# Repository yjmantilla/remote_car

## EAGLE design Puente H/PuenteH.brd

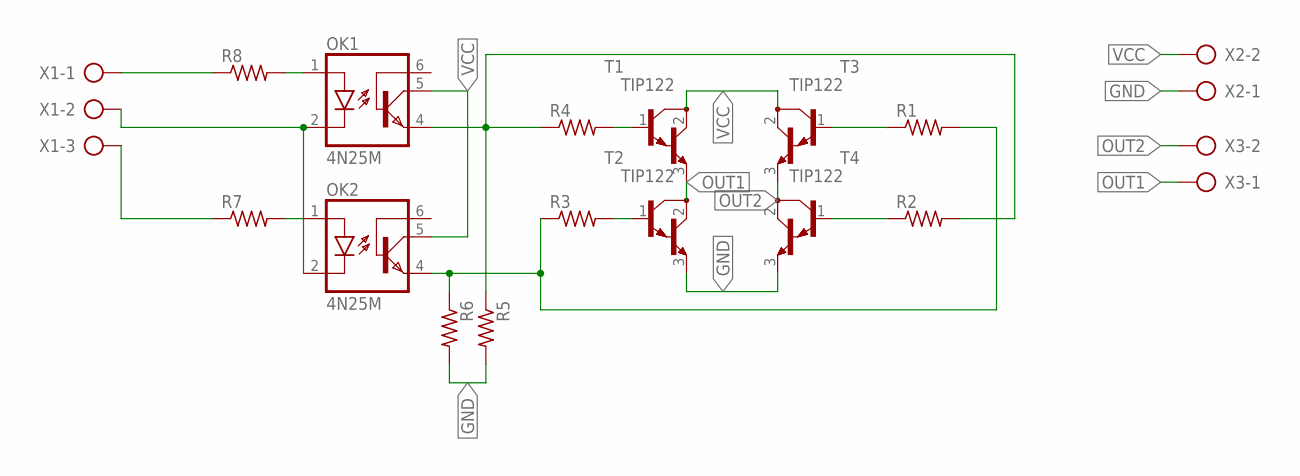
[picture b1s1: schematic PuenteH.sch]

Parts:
OK1, OK2: 4N25M; DIL06
R1, R2, R3, R4, R5, R6, R7, R8: R-US_0207/12; 0207/12
T1, T2, T3, T4: TIP122; TO220
X1: AK500/3-H
X2, X3: AK500/2-H

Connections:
GND: R5.2, R6.2, T2.3 (E), T4.3 (E), X2.1
unnamed: R4.2, T1.1 (B)
unnamed: R3.2, T2.1 (B)
unnamed: R1.1, T3.1 (B)
unnamed: R2.1, T4.1 (B)
unnamed: OK2.4 (EMI), R1.2, R3.1, R6.1
unnamed: OK1.4 (EMI), R2.2, R4.1, R5.1
unnamed: OK1.1 (A), R8.2
unnamed: OK2.1 (A), R7.2
unnamed: OK1.2 (C), OK2.2 (C), X1.2
unnamed: R7.1, X1.3
unnamed: R8.1, X1.1
OUT1: T1.3 (E), T2.2 (C), X3.1
OUT2: T3.3 (E), T4.2 (C), X3.2
VCC: OK1.5 (COL), OK2.5 (COL), T1.2 (C), T3.2 (C), X2.2

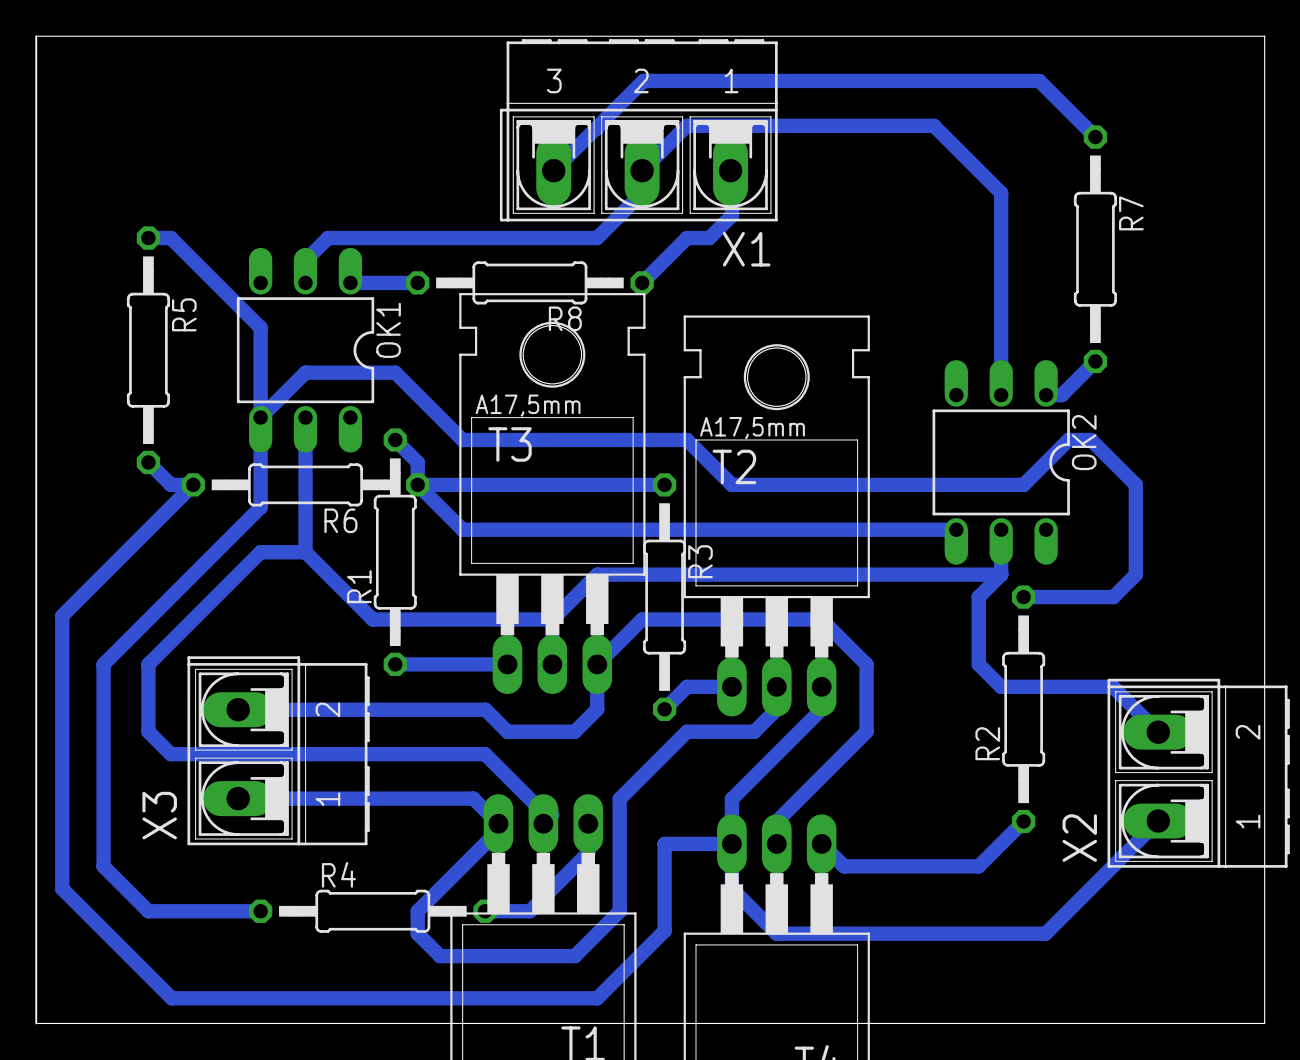
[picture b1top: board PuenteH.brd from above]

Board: 2 copper layers, 69.5 x 55.9 mm, 17 parts (0 on the bottom side), 15 nets.

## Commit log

2019-09-20 steer with DC motor
2019-10-14 some test but didnt work
2021-12-29 last
